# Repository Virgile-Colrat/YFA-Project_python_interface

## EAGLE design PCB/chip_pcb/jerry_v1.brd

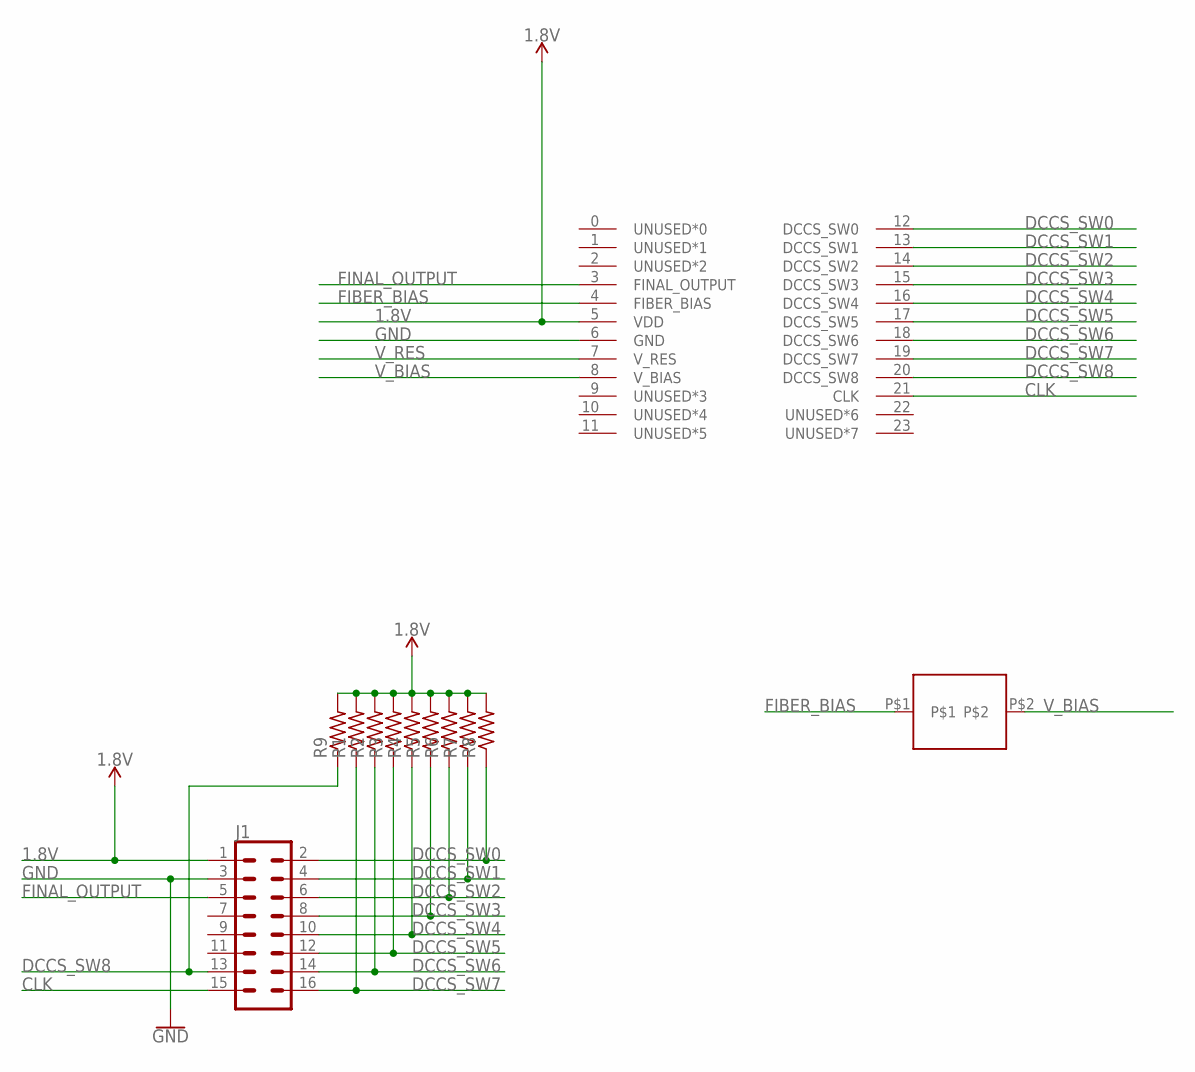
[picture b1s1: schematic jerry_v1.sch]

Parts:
J1: CONN_08X2; 2X8
R1, R2, R3, R4, R5, R6, R7, R8, R9: R-US_R0402; R0402
U$1: JERRY_V1
U$2: FIBER

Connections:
1.8V: J1.1, R1.2, R2.2, R3.2, R4.2, R5.2, R6.2, R7.2, R8.2, R9.2, U$1.5 (VDD)
CLK: J1.15, U$1.21 (CLK)
DCCS_SW0: J1.2, R8.1, U$1.12 (DCCS_SW0)
DCCS_SW1: J1.4, R7.1, U$1.13 (DCCS_SW1)
DCCS_SW2: J1.6, R6.1, U$1.14 (DCCS_SW2)
DCCS_SW3: J1.8, R5.1, U$1.15 (DCCS_SW3)
DCCS_SW4: J1.10, R4.1, U$1.16 (DCCS_SW4)
DCCS_SW5: J1.12, R3.1, U$1.17 (DCCS_SW5)
DCCS_SW6: J1.14, R2.1, U$1.18 (DCCS_SW6)
DCCS_SW7: J1.16, R1.1, U$1.19 (DCCS_SW7)
DCCS_SW8: J1.13, R9.1, U$1.20 (DCCS_SW8)
FIBER_BIAS: U$1.4 (FIBER_BIAS), U$2.P$1
FINAL_OUTPUT: J1.5, U$1.3 (FINAL_OUTPUT)
GND: J1.3, U$1.6 (GND)
V_BIAS: U$1.8 (V_BIAS), U$2.P$2
V_RES: U$1.7 (V_RES)

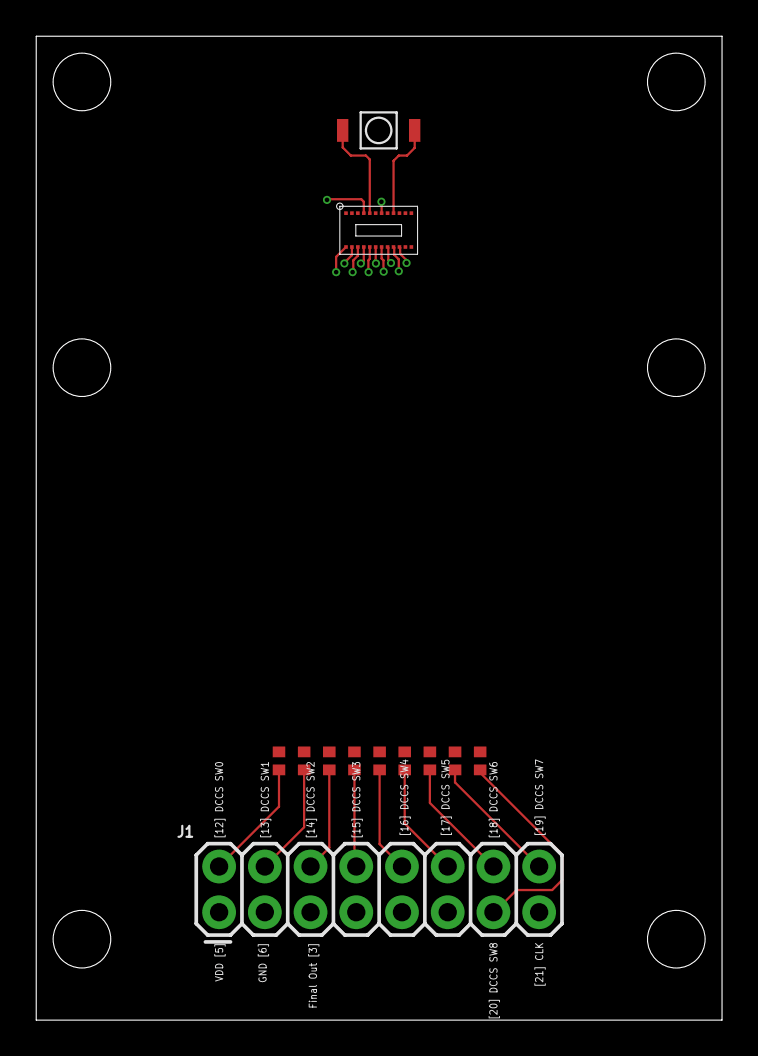
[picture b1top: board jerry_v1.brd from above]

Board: 4 copper layers, 38.1 x 54.7 mm, 12 parts (0 on the bottom side), 15 nets.

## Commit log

2020-05-18 1st update of main
2020-05-19 updated main
2020-05-19 Updated omegaette protocol doc
2020-05-19 project reorganised
2020-05-19 Serial communication added
2020-05-20 Omegaette control working
2020-05-20 3D model added
2020-05-20 MFC documentation added
2020-05-21 EOD backup
2020-05-21 backup
2020-05-22 updated documentation
2020-05-26 backup-small changes
2020-05-28 Keithley 236 control
2020-06-02 COB documentation added
2020-06-03 keithley 236 commands added
2020-06-03 Keithley cmds added
2020-06-03 keithley cmds updated
2020-06-04 System now fully functional
2020-06-08 MFC control update
2020-06-16 full project update
2020-07-06 Full system with water bath control
2020-07-06 just backup
2020-07-14 updated Matt's chip test
2020-07-22 latest update
2020-07-27 3D model update
2020-07-28 main.py updated
2020-08-07 Measurment results added
2020-08-26 updated manua
2020-08-31 Updated 3D model, LED polarization tests
2020-09-15 noise caracterization test added
2020-09-15 Test SMU 1GOhm added
2020-09-15 updated source for smu noise
2020-09-15 updated Source nois test of SMU

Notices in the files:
parts and their libraries:
SparkFun-Connectors: Licensing: Creative Commons ShareAlike 4.0 International - https://creativecommons.org/licenses/by-sa/4.0
